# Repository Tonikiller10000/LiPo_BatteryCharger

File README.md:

# LiPo_BatteryCharger

## Description
 This is a usb type C LiPo battery charger with overcharging and shortchircuits protection circuits.
 It uses the TP4056 IC to charge the battery and the DW01A with FS2805A ic\`s to protect the battery from overcharging and shortchircuits.

<table>
  <tr>
    <td></td>
    <td></td>
  </tr>
 </table>

Schematic:

Datasheets: 
- TP4056 (1A Linear Li-Ion Battery Charger): https://pdf1.alldatasheet.com/datasheet-pdf/view/1132405/ASIC/TP4056.html 
- DU01A (battery protection): https://pdf1.alldatasheet.com/datasheet-pdf/view/1150541/HMSEMI/DW01A.html
- FS8205A (Dual N-Channel MOSFET): https://pdf1.alldatasheet.com/datasheet-pdf/view/1132762/FORTUNE/FS8205A.html

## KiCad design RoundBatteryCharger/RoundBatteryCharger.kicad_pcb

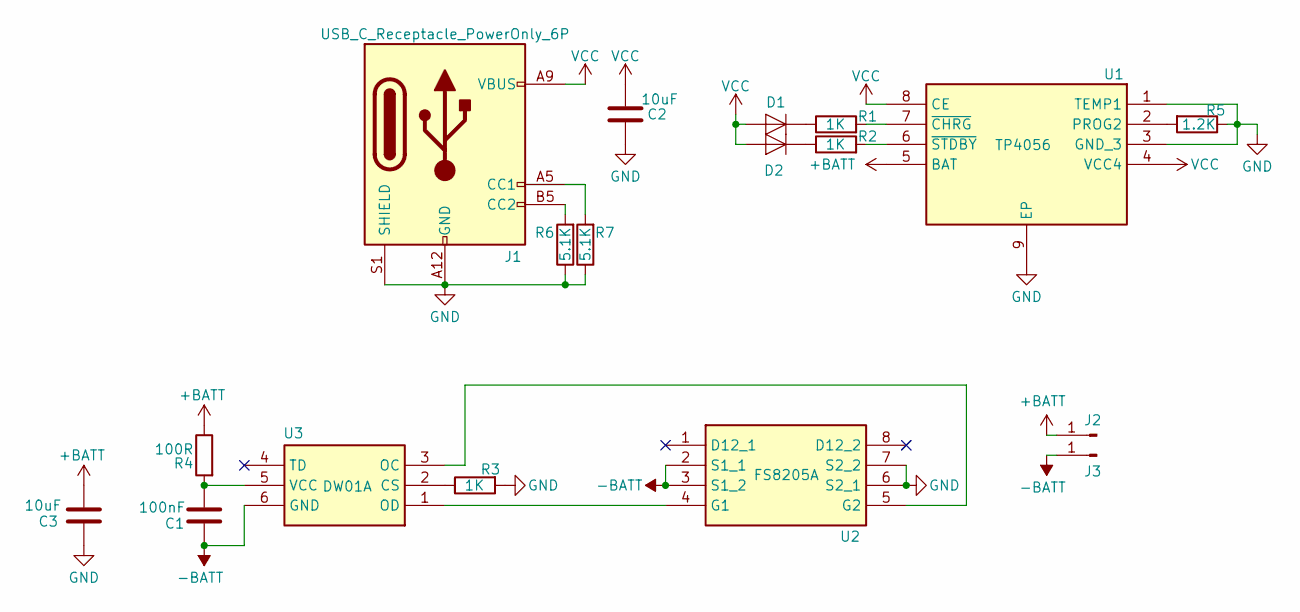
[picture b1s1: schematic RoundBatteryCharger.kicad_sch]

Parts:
C1: 100nF
C2, C3: 10uF
D1, D2: LED; LED_1206_3216Metric_Castellated
J1: USB_C_Receptacle_PowerOnly_6P; USB_C_Receptacle_GCT_USB4135-GF-A_6P_TopMnt_Horizontal
J2: Bat+
J3: Bat-
R1, R2, R3: 1K
R4: 100R
R5: 1.2K
R6, R7: 5.1K
U1: TP4056; Manufacturer_Part_Number TP4056
U2: FS8205A; Manufacturer_Part_Number FS8205A
U3: DW01A; Manufacturer_Part_Number DW01A-G

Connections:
+BATT: C3.1, J2.1, R4.1, U1.5 (BAT)
-BATT: C1.1, J3.1, U2.2 (S1_1), U2.3 (S1_2), U3.6 (GND)
GND: C2.1, C3.2, J1.A12 (GND), J1.B12 (GND), J1.S1 (SHIELD), R3.2, R5.1, R6.1, R7.1, U1.1 (TEMP1), U1.3 (GND_3), U1.9 (EP), U2.6 (S2_1), U2.7 (S2_2)
unnamed: D1.1 (K), R1.1
unnamed: D2.1 (K), R2.1
unnamed: J1.A5 (CC1), R7.2
unnamed: J1.B5 (CC2), R6.2
unnamed: R5.2, U1.2 (PROG2)
unnamed: R1.2, U1.7 (~CHRG)
unnamed: R2.2, U1.6 (~STDBY)
unnamed: U2.4 (G1), U3.1 (OD)
unnamed: U2.5 (G2), U3.3 (OC)
unnamed: R3.1, U3.2 (CS)
unnamed: C1.2, R4.2, U3.5 (VCC)
VCC: C2.2, D1.2 (A), D2.2 (A), J1.A9 (VBUS), J1.B9 (VBUS), U1.4 (VCC4), U1.8 (CE)

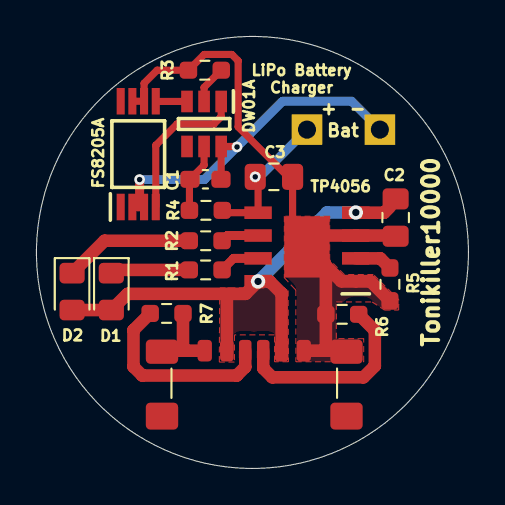
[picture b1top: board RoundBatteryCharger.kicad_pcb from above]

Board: 2 copper layers, 24.0 x 24.0 mm, 18 parts (0 on the bottom side), 15 nets.
